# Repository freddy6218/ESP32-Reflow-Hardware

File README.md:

# ESP32-Reflow-Hardware
KiCAD files for ESP32-Reflow

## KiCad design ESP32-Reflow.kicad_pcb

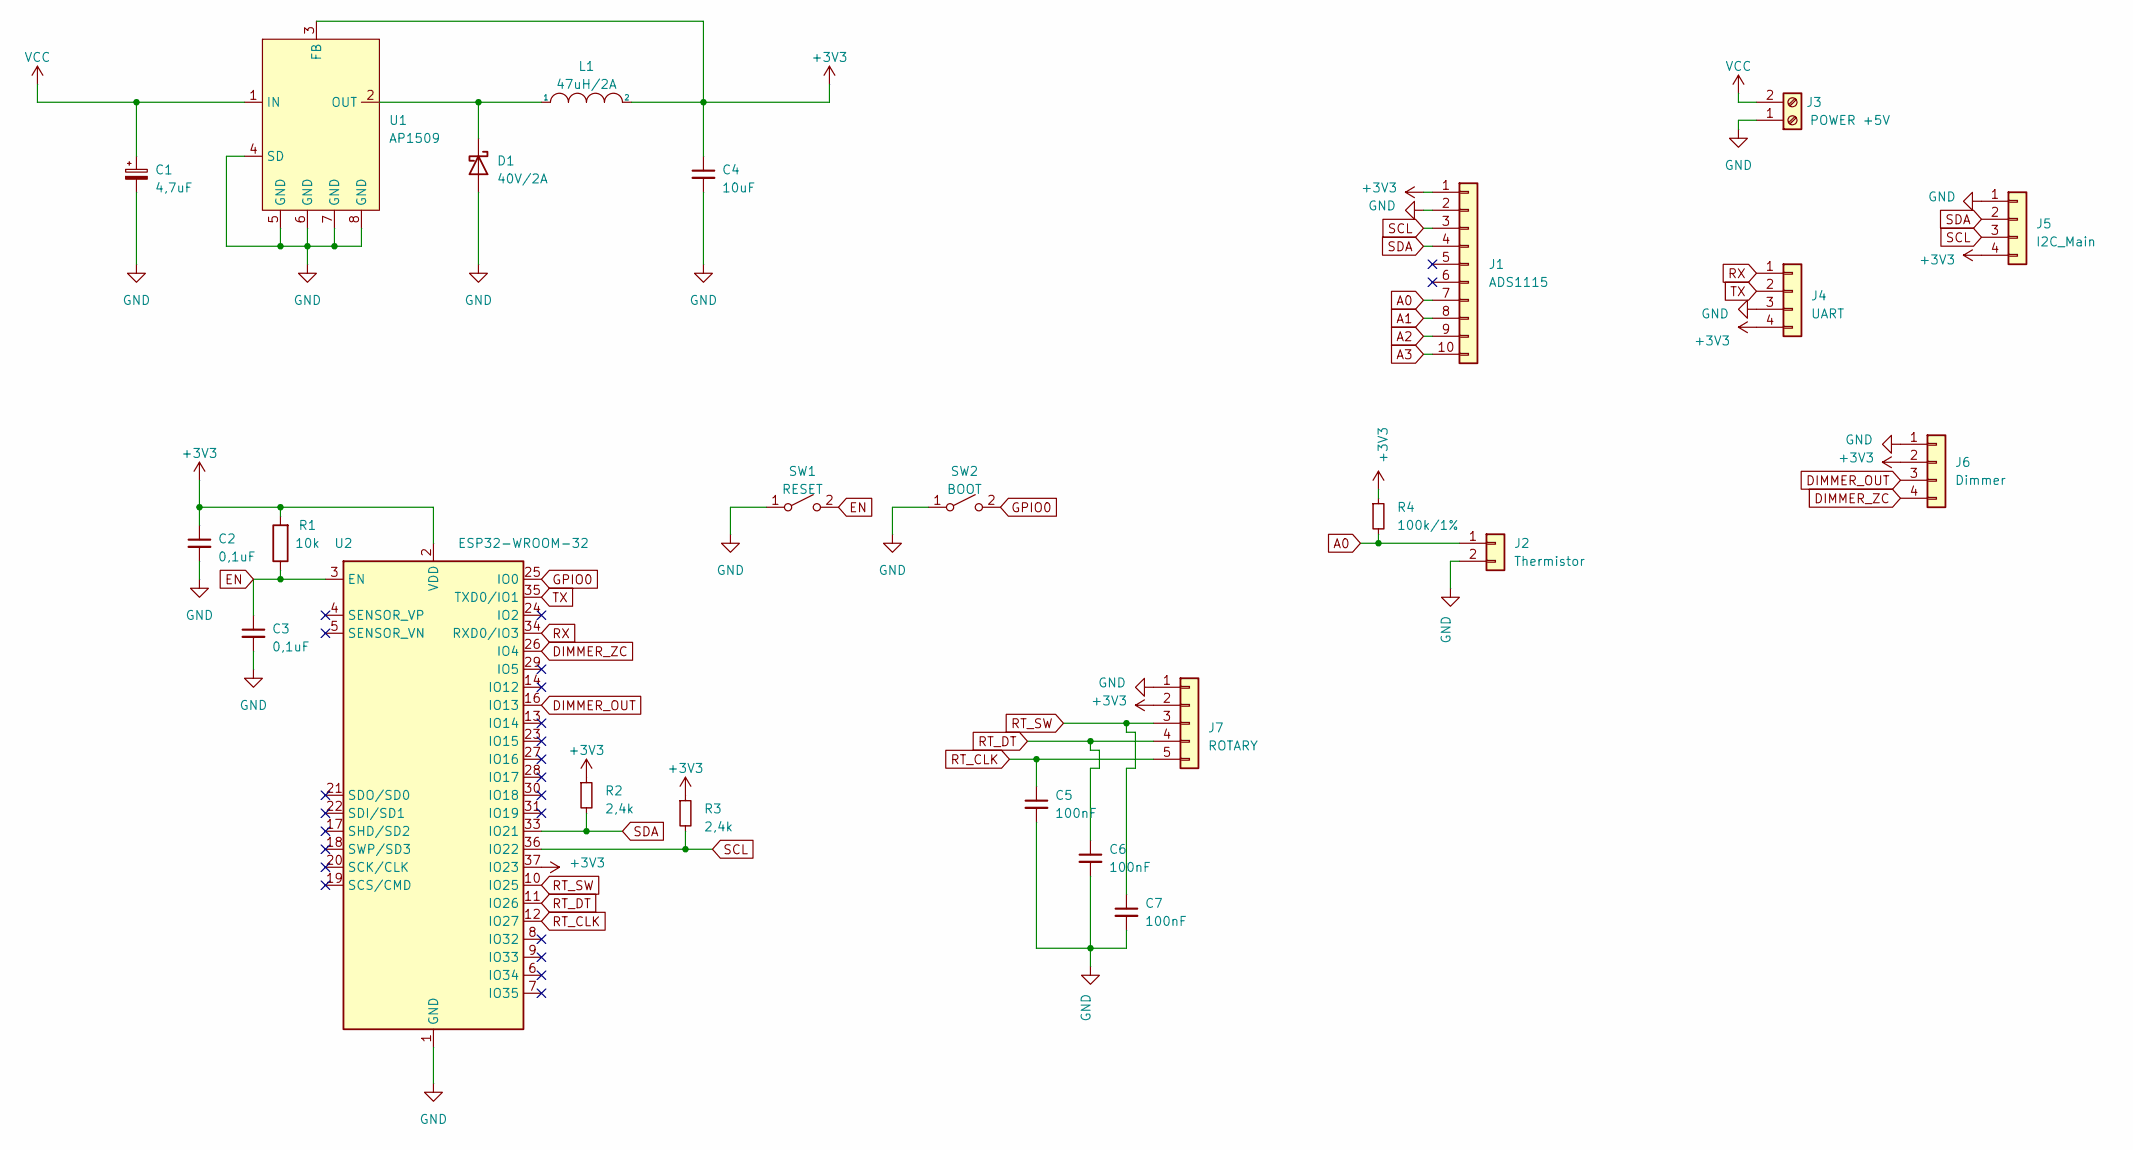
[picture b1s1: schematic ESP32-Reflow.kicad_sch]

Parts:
C1: 4,7uF; CP_Elec_5x5.3; PARTREV XXX
C2, C3: 0,1uF; C_0603_1608Metric_Pad1.08x0.95mm_HandSolder; PARTREV XXX
C4: 10uF; CP_Elec_5x5.4; PARTREV XXX
C5, C6, C7: 100nF; C_0603_1608Metric_Pad1.08x0.95mm_HandSolder
D1: 40V/2A; D_SMA_Handsoldering; PARTREV XXX
J1: ADS1115; PinHeader_1x10_P2.54mm_Vertical; PARTREV XXX
J2: Thermistor; JST_XH_B2B-XH-A_1x02_P2.50mm_Vertical; PARTREV XXX
J3: POWER +5V; JST_XH_B2B-XH-A_1x02_P2.50mm_Vertical; PARTREV XXX
J4: UART; JST_XH_B4B-XH-A_1x04_P2.50mm_Vertical; PARTREV XXX
J5: I2C_Main; JST_XH_B4B-XH-A_1x04_P2.50mm_Vertical; PARTREV XXX
J6: Dimmer; JST_XH_B4B-XH-A_1x04_P2.50mm_Vertical; PARTREV XXX
J7: ROTARY; JST_XH_B5B-XH-A_1x05_P2.50mm_Vertical; PARTREV XXX
L1: 47uH/2A; HPI1040; PARTREV XXX
R1: 10k; R_0603_1608Metric_Pad0.98x0.95mm_HandSolder; PARTREV XXX
R2, R3: 2,4k; R_0603_1608Metric_Pad0.98x0.95mm_HandSolder; PARTREV XXX
R4: 100k/1%; R_0603_1608Metric_Pad0.98x0.95mm_HandSolder
SW1: RESET; SW_SPST_FSMSM; PARTREV XXX
SW2: BOOT; SW_SPST_FSMSM; PARTREV XXX
U1: AP1509; SOP-8_3.9x4.9mm_P1.27mm; PARTREV XXX
U2: ESP32-WROOM-32; PARTREV XXX

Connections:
+3V3: C2.1, C4.1, J1.1, J4.4, J5.4, J6.2, J7.2, L1.2, R1.2, R2.1, R3.1, R4.1, U1.3 (FB), U2.2 (VDD), U2.37 (IO23)
A0: J1.7, J2.1, R4.2
A1: J1.8
A2: J1.9
A3: J1.10
DIMMER_OUT: J6.3, U2.16 (IO13)
DIMMER_ZC: J6.4, U2.26 (IO4)
EN: C3.1, R1.1, SW1.2 (B), U2.3 (EN)
GND: C1.2, C2.2, C3.2, C4.2, C5.2, C6.2, C7.2, D1.2 (A), J1.2, J2.2, J3.1, J4.3, J5.1, J6.1, J7.1, SW1.1 (A), SW2.1 (A), U1.4 (SD), U1.5 (GND), U1.6 (GND), U1.7 (GND), U1.8 (GND), U2.1 (GND), U2.15 (GND), U2.38 (GND), U2.39 (GND)
GPIO0: SW2.2 (B), U2.25 (IO0)
unnamed: D1.1 (K), L1.1, U1.2 (OUT)
RT_CLK: C5.1, J7.5, U2.12 (IO27)
RT_DT: C6.1, J7.4, U2.11 (IO26)
RT_SW: C7.1, J7.3, U2.10 (IO25)
RX: J4.1, U2.34 (RXD0/IO3)
SCL: J1.3, J5.3, R3.2, U2.36 (IO22)
SDA: J1.4, J5.2, R2.2, U2.33 (IO21)
TX: J4.2, U2.35 (TXD0/IO1)
VCC: C1.1, J3.2, U1.1 (IN)

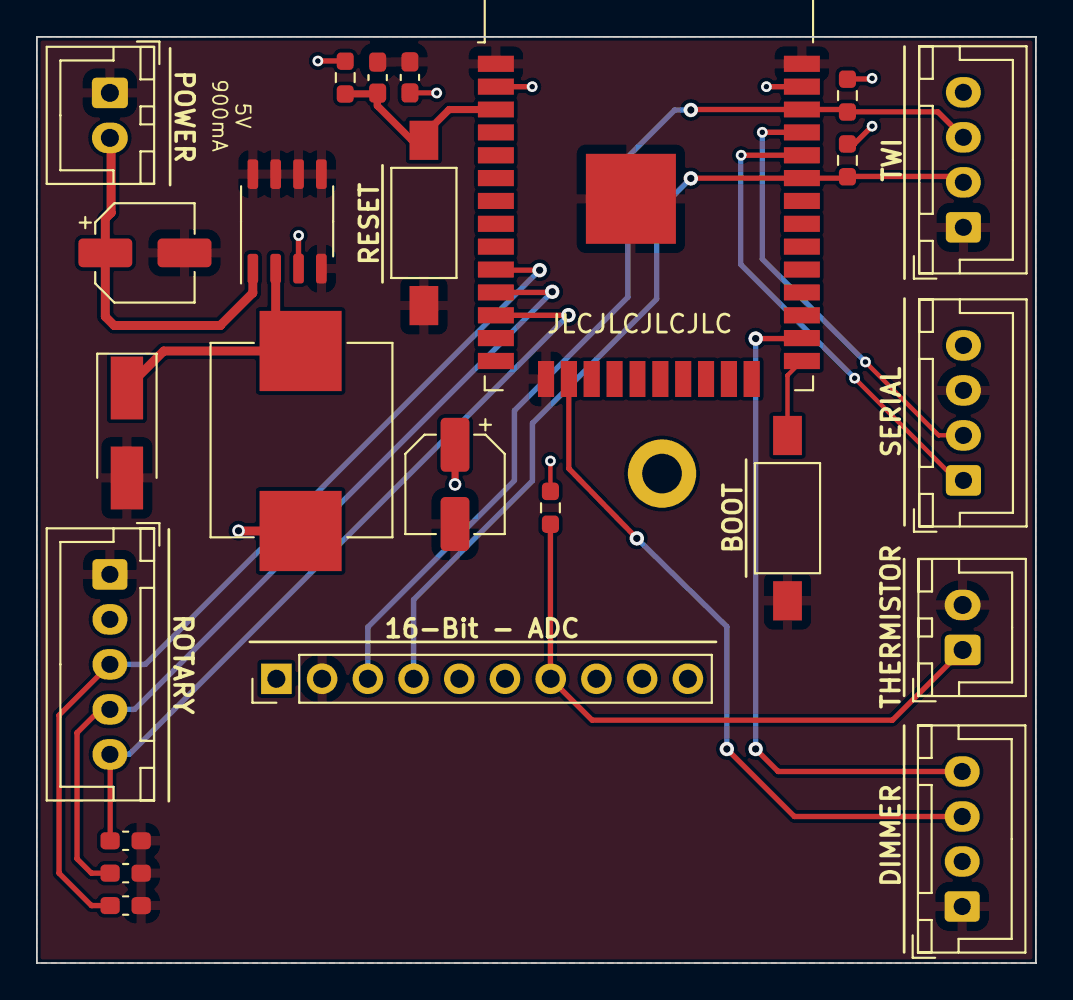
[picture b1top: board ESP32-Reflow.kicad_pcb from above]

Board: 2 copper layers, 55.5 x 51.5 mm, 24 parts (0 on the bottom side), 16 nets.

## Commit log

2021-06-27 init
